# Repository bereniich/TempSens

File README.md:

# Temperature Sensing System of HV Battery
Temperature Sensing System of HV Battery in vehicle produced by Formula Student team "Black Hornets" from the University of Novi Sad.

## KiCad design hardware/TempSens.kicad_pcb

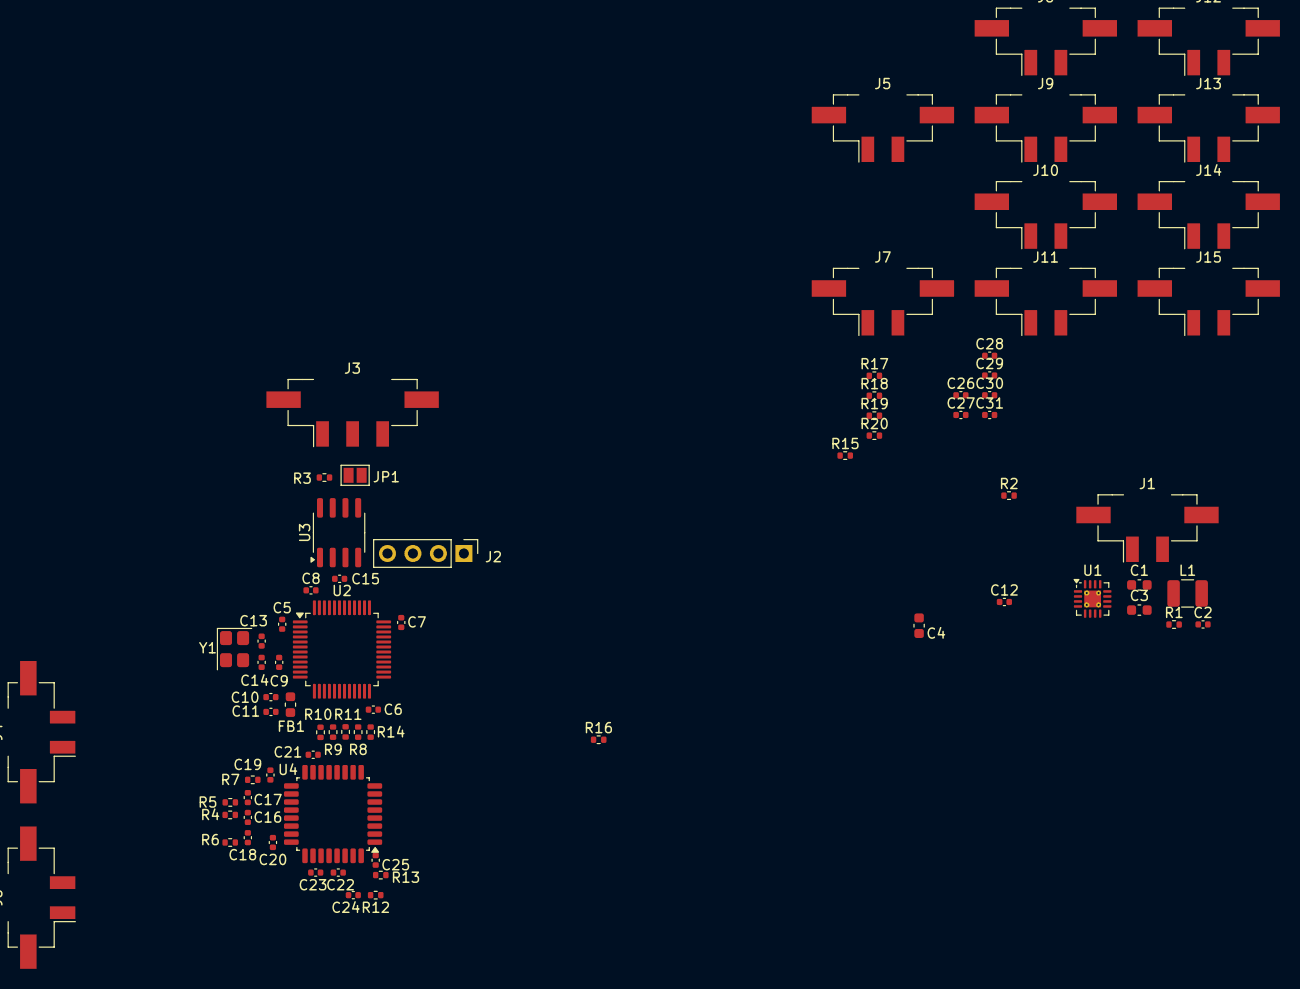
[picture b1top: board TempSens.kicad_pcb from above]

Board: 2 copper layers, 74 parts (0 on the bottom side), 52 nets, no tracks yet.

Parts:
C1, C4: 10u; C_0603_1608Metric
C2: 3.2n; C_0402_1005Metric
C3: 22u; C_0603_1608Metric
C5, C6, C7, C8, C12, C15: 100n; C_0402_1005Metric
C9: 10n; C_0402_1005Metric
C10, C11, C20, C21, C22: 1u; C_0402_1005Metric
C13, C14: 10p; C_0402_1005Metric
C16, C17, C18, C19, C23, C24, C25, C26, C27, C28, C29, C30, C31: 330n; C_0402_1005Metric
FB1: FerriteBead; L_0603_1608Metric
J1, J4, J5, J6, J7, J8, J9, J10, J11, J12, J13, J14, J15: Conn_01x02_Pin; Molex_Micro-Fit_3.0_43650-0224_1x02-1MP_P3.00mm_Vertical
J2: Conn_01x04_Pin; PinHeader_1x04_P2.54mm_Vertical
J3: Conn_01x03_Pin; Molex_Micro-Fit_3.0_43650-0324_1x03-1MP_P3.00mm_Vertical
JP1: Jumper_2_Open; SolderJumper-2_P1.3mm_Open_Pad1.0x1.5mm
L1: 2.2u; L_1210_3225Metric
R1: 100k; R_0402_1005Metric
R2: 10k; R_0402_1005Metric
R3: 120; R_0402_1005Metric
R4, R5, R6, R7, R12, R13, R15, R16, R17, R18, R19, R20: 4.7k; R_0402_1005Metric
R8, R9, R10, R11, R14: 47; R_0402_1005Metric
U1: TPS62152; VQFN-16-1EP_3x3mm_P0.5mm_EP1.68x1.68mm_ThermalVias
U2: STM32F103C8T6; LQFP-48_7x7mm_P0.5mm
U3: SN65HVD232; SOIC-8_3.9x4.9mm_P1.27mm
U4: ADS114S08B; TQFP-32_7x7mm_P0.8mm
Y1: 16MHz; Crystal_SMD_3225-4Pin_3.2x2.5mm

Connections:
+3.3V: C3.1, C4.1, C5.1, C6.1, C7.1, C8.1, C11.1, C15.1, C21.1, C22.1, C23.1, FB1.2, J2.1, L1.2, R1.1, U1.14 (VOS), U2.1 (VBAT), U2.24 (VDD), U2.36 (VDD), U2.48 (VDD), U3.3 (VCC), U4.15 (IOVDD), U4.16 (DVDD), U4.26 (AVDD), U4.30 (REFN0)
+3.3VA: C9.1, C10.1, FB1.1, U2.9 (VDDA)
/adc_rc/RESET: R8.2, U2.19 (PB1)
/adc_rc/SPI_MISO: R9.1, U2.16 (PA6)
/adc_rc/SPI_MOSI: R11.2, U2.17 (PA7)
/adc_rc/SPI_SCLK: R10.2, U2.15 (PA5)
/adc_rc/START_SYNC: R14.2, U2.20 (PB2)
/mcu_can/BOOT0: R2.2, U2.44 (BOOT0)
/mcu_can/CAN_H: J3.1, R3.1, U3.7 (CANH)
/mcu_can/CAN_L: J3.2, JP1.2 (B), U3.6 (CANL)
/mcu_can/CAN_RX: U2.45 (PB8), U3.4 (R)
/mcu_can/CAN_TX: U2.46 (PB9), U3.1 (D)
/mcu_can/HSE_IN: C13.1, U2.5 (PD0), Y1.1
/mcu_can/HSE_OUT: C14.1, U2.6 (PD1), Y1.3
/mcu_can/NRST: C12.2, U2.7 (NRST)
/mcu_can/SWCLK: J2.3, U2.37 (PA14)
/mcu_can/SWDIO: J2.2, U2.34 (PA13)
GND: C1.2, C2.2, C3.2, C4.2, C5.2, C6.2, C7.2, C8.2, C9.2, C10.2, C11.2, C12.1, C13.2, C14.2, C15.2, C16.2, C17.2, C18.2, C19.2, C20.2, C21.2, C22.2, C23.2, C24.2, C25.2, C26.2, C27.2, C28.2, C29.2, C30.2, C31.2, J1.2, J2.4, J3.3, J4.2, J5.2, J6.2, J7.2, J8.2, J9.2, J10.2, J11.2, J12.2, J13.2, J14.2, J15.2, R2.1, U1.5 (FB), U1.6 (GND), U1.7 (FSW), U1.8 (DEF), U1.9 (SS/TR), U1.15 (GND), U1.16 (GND), U1.17 (GND), U2.8 (VSSA), U2.23 (VSS), U2.35 (VSS), U2.47 (VSS), U3.2 (GND), U4.1 (AINCOM), U4.9 (~CS), U4.14 (DGND), U4.17 (CLK), U4.24 (REFCOM), U4.27 (AVSS), U4.28 (AVSS), U4.29 (REFN0), Y1.2, Y1.4
unnamed: C1.1, C2.1, J1.1, U1.10 (VIN), U1.11 (VIN), U1.12 (VIN), U1.13 (EN)
unnamed: J4.1, R4.1
unnamed: J5.1, R5.1
unnamed: J6.1, R6.1
unnamed: J7.1, R7.1
unnamed: J8.1, R12.1
unnamed: J9.1, R13.1
unnamed: J10.1, R15.1
unnamed: J11.1, R16.1
unnamed: J12.1, R17.1
unnamed: J13.1, R18.1
unnamed: J14.1, R19.1
unnamed: J15.1, R20.1
unnamed: JP1.1 (A), R3.2
unnamed: L1.1, U1.1 (SW), U1.2 (SW), U1.3 (SW)
unnamed: R1.2, U1.4 (PG)
unnamed: C27.1, R16.2, U4.7 (AIN0)
unnamed: C29.1, R18.2, U4.6 (AIN1)
unnamed: C31.1, R20.2, U4.5 (AIN2)
unnamed: C30.1, R19.2, U4.4 (AIN3)
unnamed: C28.1, R17.2, U4.3 (AIN4)
unnamed: C26.1, R15.2, U4.2 (AIN5)
unnamed: R11.1, U4.10 (DIN)
unnamed: R9.2, U4.12 (DOUT/~DRDY)
unnamed: C18.1, R6.2, U4.22 (GPIO0/AIN8)
unnamed: C16.1, R4.2, U4.21 (GPIO1/AIN9)
unnamed: C17.1, R5.2, U4.20 (GPIO2/AIN10)
unnamed: C19.1, R7.2, U4.19 (GPIO3/AIN11)
unnamed: C24.1, R12.2, U4.31 (REFN1/AIN7)
unnamed: C20.1, U4.23 (REFOUT)
unnamed: C25.1, R13.2, U4.32 (REFP1/AIN6)
unnamed: R10.1, U4.11 (SCLK)
unnamed: R14.1, U4.8 (START/SYNC)
unnamed: R8.1, U4.18 (~RESET)

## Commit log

2026-04-25 Initial clean commit with proper structure
2026-04-25 Clean project: remove backups and duplicates
2026-04-25 Added some comments
